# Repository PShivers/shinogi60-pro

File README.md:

# Shinogi60 Pro

A custom 60% mechanical keyboard PCB that fuses design elements from katana60-pro and tsuka60-pro projects.

## Name Origin

**Shinogi** (鎬) refers to the ridge line on a Japanese sword blade where both sides meet - symbolizing the fusion of design elements from both predecessor projects.

## Project Status

🚧 **In Development** - This project is currently in the initial design phase.

## Features

- **Layout**: 60% keyboard layout
- **Microcontroller**: nice!nano v2 (nRF52840-based, Bluetooth LE)
- **Connectivity**: Wireless (Bluetooth) + USB-C charging
- **Firmware**: ZMK (Zephyr-based Modern Keyboard firmware)
- **Switches**: MX-compatible hotswap sockets (no soldering required)
- **Lighting**: Optional SK6812 MINI-E RGB LEDs (per-key, reverse-mount)
- **Stabilizers**: PCB-mount stabilizers
- **Battery**: LiPo battery support for wireless operation
- **Power Management**: On/off switch, battery charging circuit
- **Manufacturing**: Optimized for JLCPCB production

## Requirements

- **KiCad 6.0 or later** - [Download here](https://www.kicad.org/download/)
- Git (for cloning with submodules)

## Getting Started

### Clone the Repository

```bash
git clone --recursive https://github.com/yourusername/shinogi60-pro.git
cd shinogi60-pro
```

If you already cloned without `--recursive`, initialize submodules:

```bash
git submodule update --init --recursive
```

### Open in KiCad

```bash
kicad shinogi60-pro.kicad_pro
```

Or open `shinogi60-pro.kicad_pro` directly in KiCad GUI.

## Project Structure

```
shinogi60-pro/
├── shinogi60-pro.kicad_pro    # KiCad project file (open this)
├── shinogi60-pro.kicad_sch    # Schematic
├── shinogi60-pro.kicad_pcb    # PCB layout
├── Libraries/                 # Component libraries (submodules)
│   ├── MX_Alps_Hybrid/       # Switch footprints
│   ├── marbastlib/           # Keyboard components
│   └── Type-C.pretty/        # USB-C connectors
├── jlcpcb/                   # Manufacturing files
│   ├── gerber/               # Gerber files for PCB fab
│   └── production_files/     # BOM & placement files
├── images/                   # Renders and layouts
├── CLAUDE.md                 # Developer documentation
└── README.md                 # This file
```

## Libraries

This project uses the following open-source libraries:

- **[MX_Alps_Hybrid](https://github.com/ai03-2725/MX_Alps_Hybrid)** by ai03 - Switch footprints
- **[marbastlib](https://github.com/ebastler/marbastlib)** by ebastler/MarvFPV - Keyboard components
- **[Type-C.pretty](https://github.com/ai03-2725/Type-C.pretty)** by ai03 - USB-C connectors

## Manufacturing

This PCB is designed for manufacturing at [JLCPCB](https://jlcpcb.com/) with their SMT assembly service.

### Export Production Files

1. **Gerber Files**: File → Plot → Generate Gerber and drill files
2. **BOM**: Tools → Generate BOM
3. **CPL**: File → Fabrication Outputs → Component Placement (.pos)

Production-ready files will be saved in the `jlcpcb/` directory.

### PCB Specifications

- **Size**: TBD (60% layout)
- **Layers**: 2-layer PCB
- **Thickness**: 1.6mm
- **Finish**: HASL / ENIG (recommended for better durability)
- **Color**: Your choice

## Design Philosophy

Shinogi60 Pro combines:

- Refined circuit design from predecessor projects
- Wireless-first design with Bluetooth LE (nice!nano)
- Battery-powered for true cable-free operation
- Optional per-key RGB lighting
- Hotswap sockets for easy switch replacement
- USB-C for charging and wired fallback
- Pro Micro footprint for controller compatibility

## Development

### Before Manufacturing

1. Run Design Rule Check: `Tools → Design Rules Checker`
2. Review 3D view for mechanical clearances
3. Verify all footprints against datasheets
4. Double-check BOM part numbers (LCSC availability)
5. Peer review recommended

### Contributing

This is a personal project, but suggestions and improvements are welcome! Please open an issue to discuss changes.

## Firmware

This keyboard will run **[ZMK Firmware](https://zmk.dev/)** - a modern, wireless-first keyboard firmware built on the Zephyr RTOS.

### ZMK Features

- Native Bluetooth LE support
- Low power consumption for extended battery life
- Advanced features (layers, combos, macros, mod-tap)
- GitHub Actions-based build system
- Active development and community

_Firmware configuration will be added after hardware validation._

### nice!nano

The [nice!nano](https://nicekeyboards.com/nice-nano/) is a Pro Micro-compatible wireless controller:

- Based on nRF52840 (ARM Cortex-M4, 64MHz)
- Built-in Bluetooth 5.0 LE
- USB-C connector for charging/data
- Battery management circuitry
- ZMK firmware pre-installed

## License

MIT License - See [LICENSE](LICENSE) file for details.

Copyright (c) 2022 Baris Tosun

## Acknowledgments

- **ai03** - For MX_Alps_Hybrid and Type-C libraries
- **ebastler & MarvFPV** - For marbastlib
- The keyboard community for open-source resources and inspiration

## Related Projects

- [katana60-pro](../katana60-pro/) - Predecessor project
- [tsuka60-pro](../tsuka60-pro.kicad/) - Predecessor project

---

**Shinogi60 Pro** - Where design elements meet at the ridge line.

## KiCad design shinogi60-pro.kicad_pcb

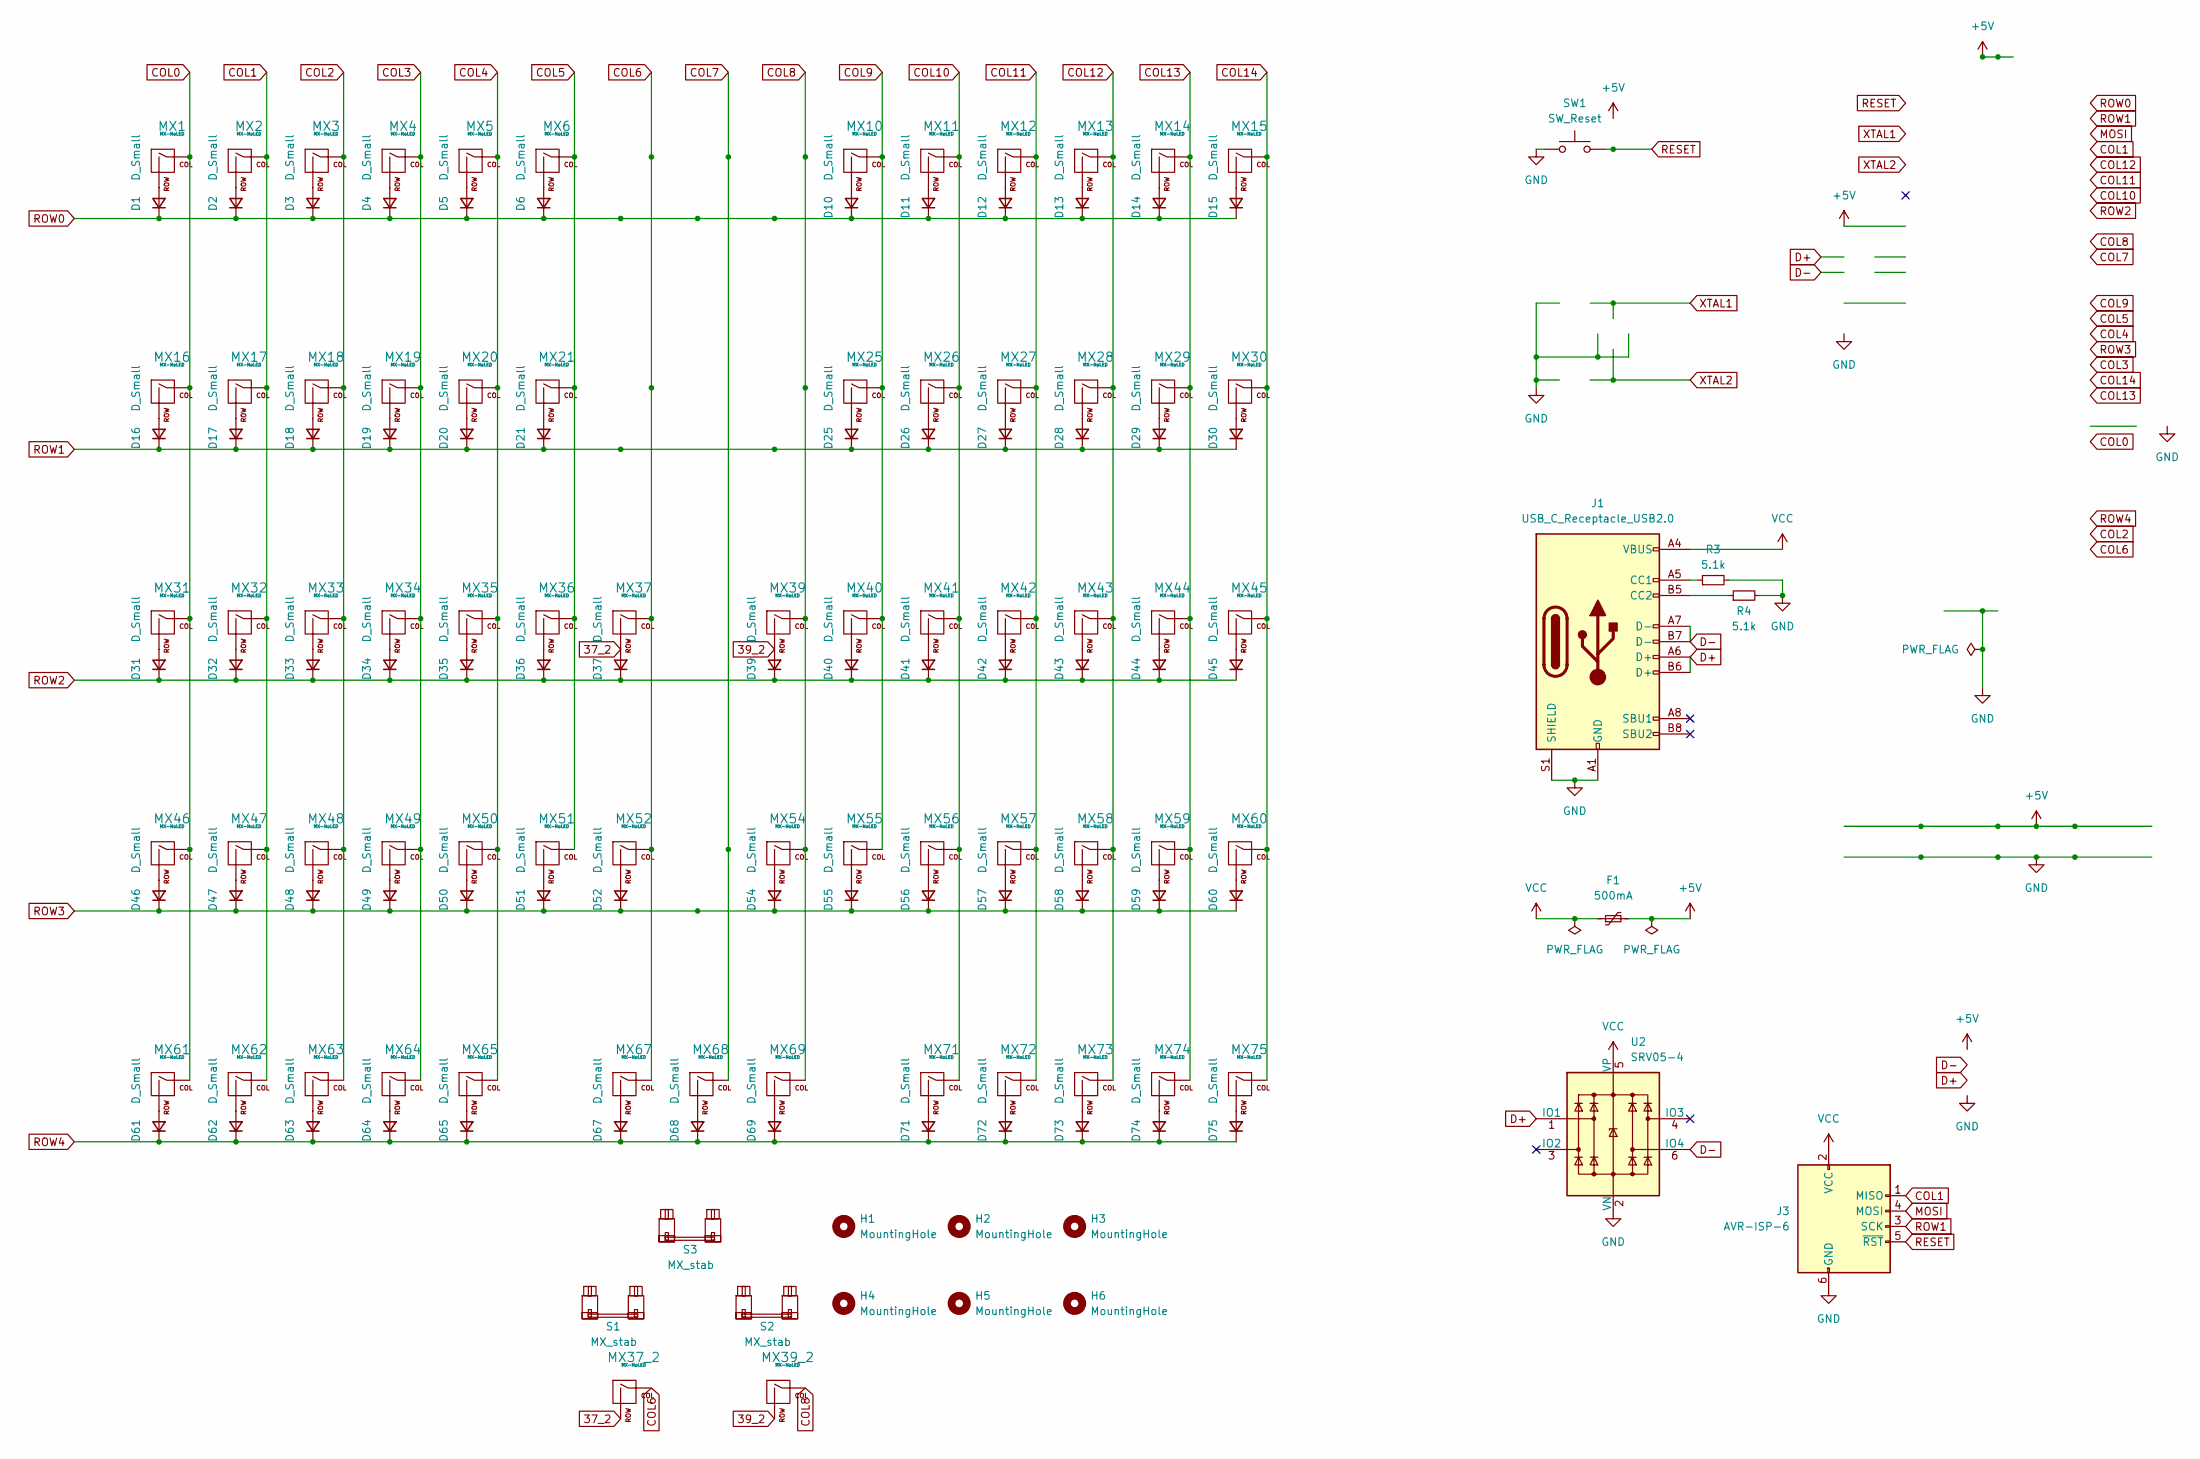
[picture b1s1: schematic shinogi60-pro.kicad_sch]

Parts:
D1, D2, D3, D4, D5, D6, D10, D11, D12, D13, D14, D15, D16, D17, D18, D19, D20, D21, D25, D26, D27, D28, D29, D30, D31, D32, D33, D34, D35, D36, D37, D39, D40, D41, D42, D43, D44, D45, D46, D47, D48, D49, D50, D51, D52, D54, D55, D56, D57, D58, D59, D60, D61, D62, D63, D64, D65, D67, D68, D69, D71, D72, D73, D74, D75: D_Small; D_SOD-123
F1: 500mA; Fuse_1206_3216Metric_Pad1.42x1.75mm_HandSolder
H1, H2, H3, H4, H5, H6: MountingHole; MountingHole_2.2mm_M2_Pad_TopOnly
J1: USB_C_Receptacle_USB2.0; USB_C_Receptacle_HRO_TYPE-C-31-M-12
J3: AVR-ISP-6; PinHeader_2x03_P2.54mm_Horizontal
MX1, MX15, MX16, MX30, MX31, MX37_2, MX39_2, MX45: MX-NoLED; SW_MX_HS_1.25u
MX2, MX3, MX4, MX5, MX6, MX10, MX11, MX12, MX13, MX14, MX17, MX18, MX19, MX20, MX21, MX25, MX26, MX27, MX28, MX29, MX32, MX33, MX34, MX35, MX36, MX37, MX39, MX40, MX41, MX42, MX43, MX44, MX46, MX47, MX48, MX49, MX50, MX51, MX52, MX54, MX55, MX56, MX57, MX58, MX59, MX60, MX61, MX62, MX63, MX64, MX65, MX67, MX68, MX69, MX71, MX72, MX73, MX74, MX75: MX-NoLED; SW_MX_HS_1u
R3, R4: 5.1k; C_0603_1608Metric_Pad1.08x0.95mm_HandSolder
S1, S2: MX_stab; STAB_MX_2u
S3: MX_stab; STAB_MX_7u
SW1: SW_Reset; SW_SPST_SKQG_WithStem
U2: SRV05-4; SOT-23-6

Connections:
37_2: D37.2 (A), MX37.2 (ROW), MX37_2.2 (ROW)
39_2: D39.2 (A), MX39.2 (ROW), MX39_2.2 (ROW)
COL0: MX1.1 (COL), MX16.1 (COL), MX31.1 (COL), MX46.1 (COL), MX61.1 (COL); also elsewhere on the board
COL1: J3.1 (MISO), MX2.1 (COL), MX17.1 (COL), MX32.1 (COL), MX47.1 (COL), MX62.1 (COL); also elsewhere on the board
COL2: MX3.1 (COL), MX18.1 (COL), MX33.1 (COL), MX48.1 (COL), MX63.1 (COL); also elsewhere on the board
COL3: MX4.1 (COL), MX19.1 (COL), MX34.1 (COL), MX49.1 (COL), MX64.1 (COL); also elsewhere on the board
COL4: MX5.1 (COL), MX20.1 (COL), MX35.1 (COL), MX50.1 (COL), MX65.1 (COL); also elsewhere on the board
COL10: MX11.1 (COL), MX26.1 (COL), MX41.1 (COL), MX56.1 (COL), MX71.1 (COL); also elsewhere on the board
COL11: MX12.1 (COL), MX27.1 (COL), MX42.1 (COL), MX57.1 (COL), MX72.1 (COL); also elsewhere on the board
COL12: MX13.1 (COL), MX28.1 (COL), MX43.1 (COL), MX58.1 (COL), MX73.1 (COL); also elsewhere on the board
COL13: MX14.1 (COL), MX29.1 (COL), MX44.1 (COL), MX59.1 (COL), MX74.1 (COL); also elsewhere on the board
COL14: MX15.1 (COL), MX30.1 (COL), MX45.1 (COL), MX60.1 (COL), MX75.1 (COL); also elsewhere on the board
GND: J1.A1 (GND), J1.A12 (GND), J1.B1 (GND), J1.B12 (GND), J1.S1 (SHIELD), J3.6 (GND), R3.2, R4.2, SW1.1, U2.2 (VN); also elsewhere on the board
unnamed: D1.2 (A), MX1.2 (ROW)
unnamed: D2.2 (A), MX2.2 (ROW)
unnamed: D3.2 (A), MX3.2 (ROW)
unnamed: D4.2 (A), MX4.2 (ROW)
unnamed: D5.2 (A), MX5.2 (ROW)
unnamed: D6.2 (A), MX6.2 (ROW)
unnamed: D10.2 (A), MX10.2 (ROW)
unnamed: D11.2 (A), MX11.2 (ROW)
unnamed: D12.2 (A), MX12.2 (ROW)
unnamed: D13.2 (A), MX13.2 (ROW)
unnamed: D14.2 (A), MX14.2 (ROW)
unnamed: D15.2 (A), MX15.2 (ROW)
unnamed: D16.2 (A), MX16.2 (ROW)
unnamed: D17.2 (A), MX17.2 (ROW)
unnamed: D18.2 (A), MX18.2 (ROW)
unnamed: D19.2 (A), MX19.2 (ROW)
unnamed: D20.2 (A), MX20.2 (ROW)
unnamed: D21.2 (A), MX21.2 (ROW)
unnamed: D25.2 (A), MX25.2 (ROW)
unnamed: D26.2 (A), MX26.2 (ROW)
unnamed: D27.2 (A), MX27.2 (ROW)
unnamed: D28.2 (A), MX28.2 (ROW)
unnamed: D29.2 (A), MX29.2 (ROW)
unnamed: D30.2 (A), MX30.2 (ROW)
unnamed: D31.2 (A), MX31.2 (ROW)
unnamed: D32.2 (A), MX32.2 (ROW)
unnamed: D33.2 (A), MX33.2 (ROW)
unnamed: D34.2 (A), MX34.2 (ROW)
unnamed: D35.2 (A), MX35.2 (ROW)
unnamed: D36.2 (A), MX36.2 (ROW)
unnamed: D40.2 (A), MX40.2 (ROW)
unnamed: D41.2 (A), MX41.2 (ROW)
unnamed: D42.2 (A), MX42.2 (ROW)
unnamed: D43.2 (A), MX43.2 (ROW)
unnamed: D44.2 (A), MX44.2 (ROW)
unnamed: D45.2 (A), MX45.2 (ROW)
unnamed: D46.2 (A), MX46.2 (ROW)
unnamed: D47.2 (A), MX47.2 (ROW)
unnamed: D48.2 (A), MX48.2 (ROW)
unnamed: D49.2 (A), MX49.2 (ROW)
unnamed: D50.2 (A), MX50.2 (ROW)
unnamed: D51.2 (A), MX51.2 (ROW)
unnamed: D52.2 (A), MX52.2 (ROW)
unnamed: D54.2 (A), MX54.2 (ROW)
unnamed: D55.2 (A), MX55.2 (ROW)
unnamed: D56.2 (A), MX56.2 (ROW)
unnamed: D57.2 (A), MX57.2 (ROW)
unnamed: D58.2 (A), MX58.2 (ROW)
unnamed: D59.2 (A), MX59.2 (ROW)
unnamed: D60.2 (A), MX60.2 (ROW)
unnamed: D61.2 (A), MX61.2 (ROW)
unnamed: D62.2 (A), MX62.2 (ROW)
unnamed: D63.2 (A), MX63.2 (ROW)
unnamed: D64.2 (A), MX64.2 (ROW)
unnamed: D65.2 (A), MX65.2 (ROW)
unnamed: D67.2 (A), MX67.2 (ROW)
unnamed: D68.2 (A), MX68.2 (ROW)
unnamed: D69.2 (A), MX69.2 (ROW)
unnamed: D71.2 (A), MX71.2 (ROW)
unnamed: D72.2 (A), MX72.2 (ROW)
unnamed: D73.2 (A), MX73.2 (ROW)
unnamed: D74.2 (A), MX74.2 (ROW)
unnamed: D75.2 (A), MX75.2 (ROW)
unnamed: F1.1, J1.A4 (VBUS), J1.A9 (VBUS), J1.B4 (VBUS), J1.B9 (VBUS), J3.2 (VCC), U2.5 (VP)
unnamed: J1.A5 (CC1), R3.1
unnamed: J1.A6 (D+), J1.B6 (D+), U2.1 (IO1)
unnamed: J1.A7 (D-), J1.B7 (D-), U2.6 (IO4)
unnamed: J1.B5 (CC2), R4.1
RESET: J3.5 (~RST), SW1.2; also elsewhere on the board
ROW4: D61.1 (K), D62.1 (K), D63.1 (K), D64.1 (K), D65.1 (K), D67.1 (K), D68.1 (K), D69.1 (K), D71.1 (K), D72.1 (K), D73.1 (K), D74.1 (K), D75.1 (K); also elsewhere on the board

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
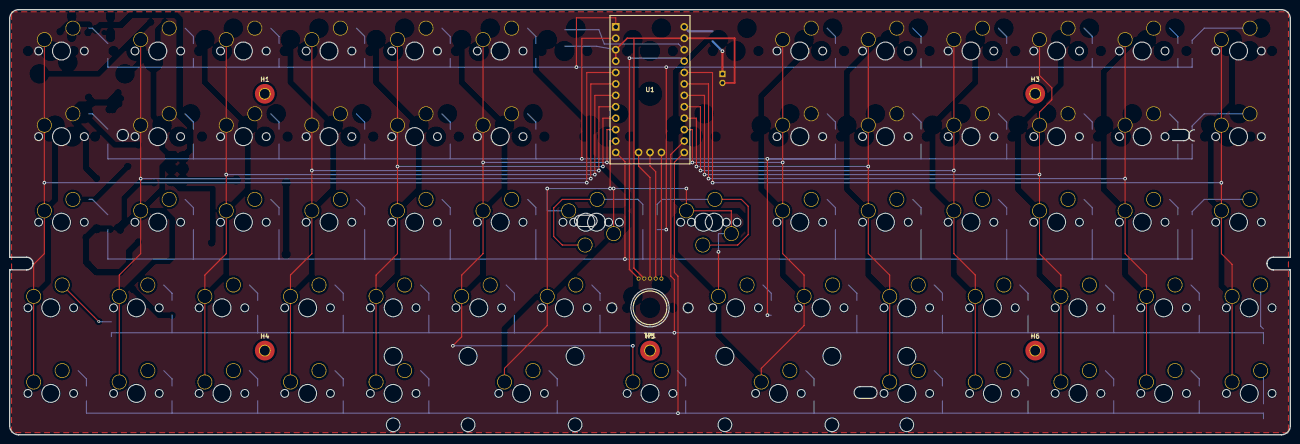
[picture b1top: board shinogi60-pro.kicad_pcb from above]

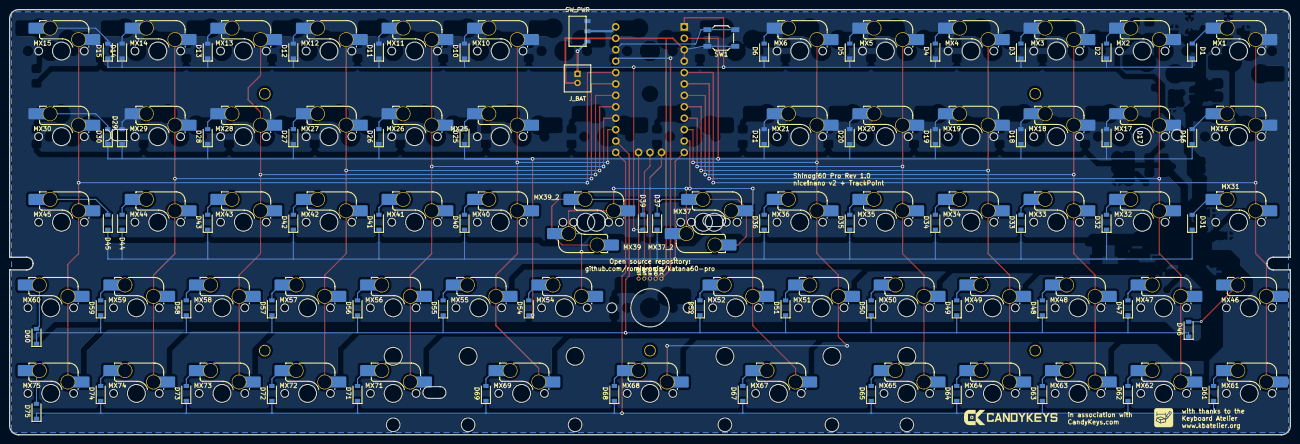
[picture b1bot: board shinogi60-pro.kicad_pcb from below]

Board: 2 copper layers, 285.0 x 94.6 mm, 145 parts (135 on the bottom side), 91 nets.

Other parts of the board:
J_BAT: LiPo_2Pin; JST_PH_2Pin
SW_PWR: MSK12C02-HB; SW_MSK12C02-HB
TP1: TrackPoint_Module; TrackPoint_Center
U1: nice!nano_v2; NiceNano_v2

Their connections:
B+: SW_PWR.2, U1.24
BAT+: J_BAT.1, SW_PWR.1
COL0: U1.5; also elsewhere on the board
COL1: U1.6; also elsewhere on the board
COL2: U1.7; also elsewhere on the board
COL3: U1.8; also elsewhere on the board
COL4: U1.9; also elsewhere on the board
COL10: U1.16; also elsewhere on the board
COL11: U1.17; also elsewhere on the board
COL12: U1.18; also elsewhere on the board
COL13: U1.19; also elsewhere on the board
COL14: U1.20; also elsewhere on the board
GND: J_BAT.2, TP1.2, U1.3, U1.4, U1.23; also elsewhere on the board
RESET: U1.22; also elsewhere on the board
ROW4: U1.13; also elsewhere on the board
TP_CLK: TP1.3, U1.25
TP_DAT: TP1.4, U1.26
TP_RST: TP1.5, U1.27
VCC: TP1.1, U1.21

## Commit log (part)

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2026-01-15 Initial project setup for Shinogi60 Pro
    - Created basic KiCad 6.0 project structure
    - Added library submodules (MX_Alps_Hybrid, Type-C.pretty, marbastlib)
    - Configured footprint and symbol library tables
    - Added CLAUDE.md with project documentation
    - Included MIT license
    - Set up directory structure for JLCPCB manufacturing
2026-01-15 Update CLAUDE.md and add README.md with project details and features
2026-01-15 Update project files for KiCad 9.0 and improve gitignore
    - Upgrade schematic and project files from KiCad 8.0 to 9.0 format
    - Add new DRC/ERC rules introduced in KiCad 9.0
    - Add *.kicad_prl and lock files (~*.lck) to gitignore
2026-01-15 Add markdownlint with VS Code format-on-save
    - Configure VS Code to auto-format markdown files on save
    - Add .markdownlint.json with relaxed rules for line length,
    inline HTML, and first-line headings
2026-01-15 and documentation for changes that need to be made from the katana and tsuka
2026-01-15 auto generated kicad files
2026-01-26 moved the top letter row around and removed the usb. made room for mcu
